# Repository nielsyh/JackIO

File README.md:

# JackIO
Project JackIO

This Project is about communication between an audiojack from a Android device to a Microprocessor.
It includes:
-Android API / GUI.
-C & c++ code for a microprocessor.
-Some documentation.
-Eegle schematics for designed/build hardware.

This project should work on any android phone and it is tested on a Atmel Atmega8L.

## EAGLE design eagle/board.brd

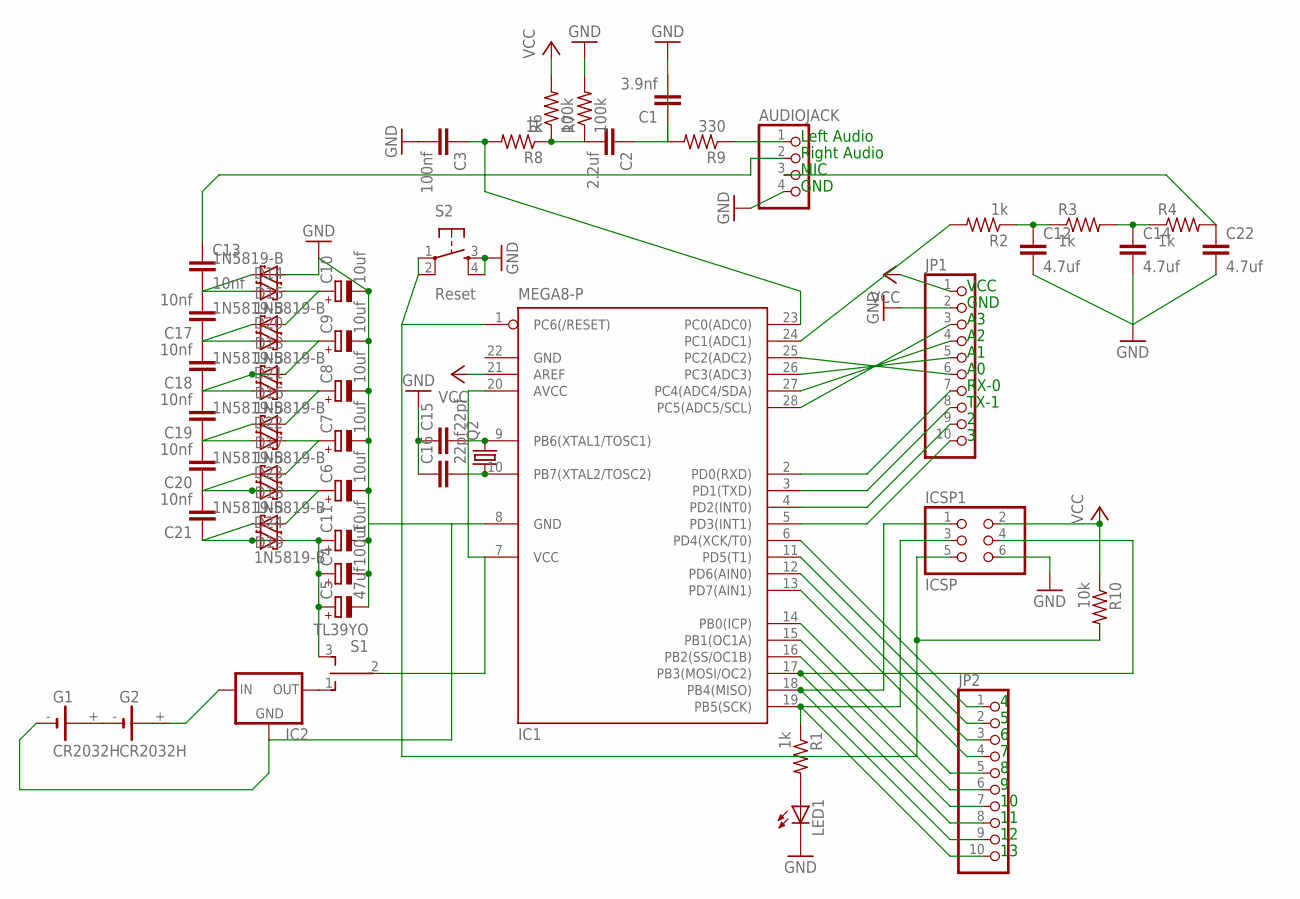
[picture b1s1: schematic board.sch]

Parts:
AUDIOJACK: PINHD-1X4; 1X04
C1: 3.9nf; C050-024X044
C2: 2.2uf; C050-024X044
C3: 100nf; C050-024X044
C4: 100uf; E2,5-6E
C5: 47uf; E2-5
C6, C7, C8, C9, C10, C11: 10uf; B45181B
C12, C14, C22: 4.7uf; C050-024X044
C13, C17, C18, C19, C20, C21: 10nf; C050-024X044
C15, C16: 22pf; C025-025X050
D13, D14, D15, D16, D17, D18, D19, D20, D21, D22, D23, D24: 1N5819-B; DO41-7.6
G1, G2: CR2032H
IC1: MEGA8-P; DIL28-3
IC2: XC63FPL; TO92
ICSP1: ICSP; 2X03
JP1, JP2: PINHD-1X10; 1X10
LED1: LED3MM
Q2: CRYSTALHC18U-V; HC18U-V
R1, R2, R3, R4, R8: 1k; 0207/10
R6, R7: 100k; 0207/10
R9: 330; 0207/10
R10: 10k; 0207/10
S1: TL39YO; TL3XYO
S2: Reset; TACTILE-PTH

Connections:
GND: AUDIOJACK.4, C1.2, C3.2, C4.-, C5.-, C6.-, C7.-, C8.-, C9.-, C10.-, C11.-, C12.2, C14.2, C15.1, C16.1, C22.2, D15.A, G1.-, IC1.8 (GND), IC1.22 (GND), IC2.2 (GND), ICSP1.6, JP1.2, LED1.K (C), R7.2, R9.2, S2.3, S2.4
unnamed: IC1.18 (PB4(MISO)), ICSP1.1, JP2.9
unnamed: AUDIOJACK.2, C13.1
unnamed: AUDIOJACK.1, R9.1
unnamed: IC1.24 (PC1(ADC1)), R2.2
unnamed: IC1.19 (PB5(SCK)), ICSP1.3, JP2.10, R1.1
unnamed: IC1.1 (PC6(/RESET)), ICSP1.5, R10.2, S2.1, S2.2
unnamed: C15.2, IC1.9 (PB6(XTAL1/TOSC1)), Q2.2
unnamed: C16.2, IC1.10 (PB7(XTAL2/TOSC2)), Q2.1
unnamed: IC2.3 (OUT), S1.1 (O)
unnamed: G1.+, G2.-
unnamed: G2.+, IC2.1 (IN)
unnamed: IC1.7 (VCC), IC1.20 (AVCC), S1.2
unnamed: C3.1, IC1.23 (PC0(ADC0)), R8.2
unnamed: LED1.A, R1.2
unnamed: C1.1, C2.1
unnamed: IC1.28 (PC5(ADC5/SCL)), JP1.3
unnamed: C12.1, R2.1, R3.1
unnamed: C14.1, R3.2, R4.1
unnamed: IC1.27 (PC4(ADC4/SDA)), JP1.4
unnamed: AUDIOJACK.3, C22.1, R4.2
unnamed: IC1.26 (PC3(ADC3)), JP1.5
unnamed: IC1.17 (PB3(MOSI/OC2)), ICSP1.4, JP2.8
unnamed: IC1.25 (PC2(ADC2)), JP1.6
unnamed: C2.2, R6.1, R7.1, R8.1
unnamed: IC1.2 (PD0(RXD)), JP1.7
unnamed: IC1.3 (PD1(TXD)), JP1.8
unnamed: IC1.4 (PD2(INT0)), JP1.9
unnamed: IC1.5 (PD3(INT1)), JP1.10
unnamed: IC1.6 (PD4(XCK/T0)), JP2.1
unnamed: IC1.11 (PD5(T1)), JP2.2
unnamed: IC1.12 (PD6(AIN0)), JP2.3
unnamed: IC1.13 (PD7(AIN1)), JP2.4
unnamed: IC1.14 (PB0(ICP)), JP2.5
unnamed: IC1.15 (PB1(OC1A)), JP2.6
unnamed: IC1.16 (PB2(SS/OC1B)), JP2.7
unnamed: C13.2, C17.2, D14.A, D15.C
unnamed: C17.1, C18.2, D13.C, D20.A
unnamed: C18.1, C19.2, D16.C, D21.A
unnamed: C19.1, C20.2, D17.C, D22.A
unnamed: C20.1, C21.2, D18.C, D23.A
unnamed: C21.1, D19.C, D24.A
unnamed: C10.+, D13.A, D14.C
unnamed: C9.+, D16.A, D20.C
unnamed: C8.+, D17.A, D21.C
unnamed: C7.+, D18.A, D22.C
unnamed: C6.+, D19.A, D23.C
unnamed: C4.+, C5.+, C11.+, D24.C, S1.3 (S)
VCC: IC1.21 (AREF), ICSP1.2, JP1.1, R6.2, R10.1

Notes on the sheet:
Left Audio
Right Audio
MIC
GND
VCC
RX-0
TX-1

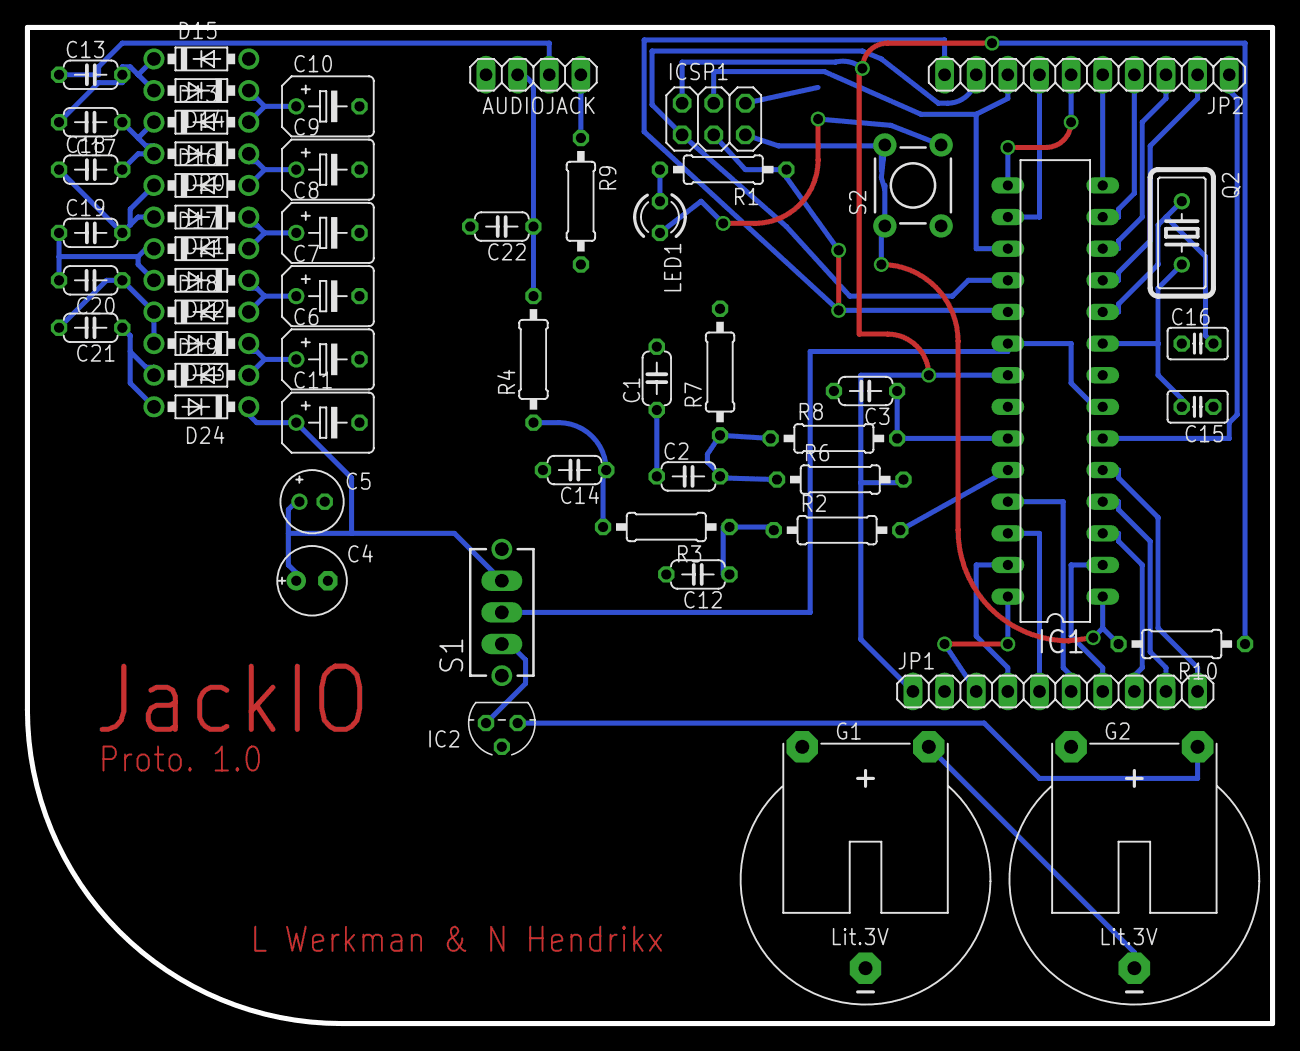
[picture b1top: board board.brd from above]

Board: 2 copper layers, 100.0 x 80.0 mm, 55 parts (0 on the bottom side), 49 nets.

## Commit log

2016-08-19 project code and docs
2016-08-19 readme.md

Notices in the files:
parts and their libraries:
SparkFun-Retired: Licensing:Creative Commons ShareAlike 4.0 International - https://creativecommons.org/licenses/by-sa/4.0
